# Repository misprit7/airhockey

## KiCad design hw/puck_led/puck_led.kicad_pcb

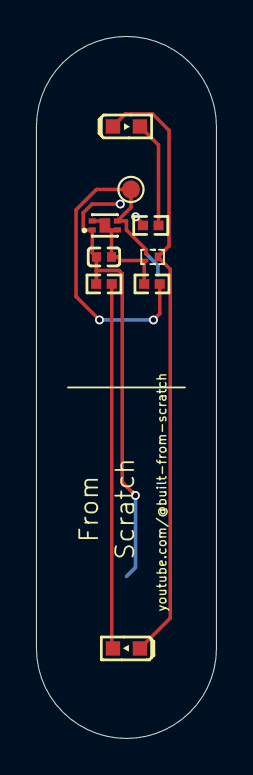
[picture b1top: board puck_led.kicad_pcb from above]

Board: 2 copper layers, 10.0 x 39.0 mm, 9 parts (0 on the bottom side), 6 nets.

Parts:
C1: 100nF; C0402
LED1, LED2: OPTO-SMD_L1.6-W0.8_E6C0603IRAC1UDA_1
Q1: PICOSTAR-3_L1.0-W0.6-P0.35-TL
R1: 100kΩ; R0402
R2, R3: 150Ω; R0402
TP1: TestPoint; TestPoint_Pad_D1.0mm
U1: XFDFN-4_L1.4-W1.1-P0.50-BL-EP

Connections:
+3V0: C1.2, R2.2, R3.2, U1.1 (VCC)
GND: C1.1, Q1.2 (S), R1.1, U1.2 (GND), U1.4 (SEL), U1.5 (EP)
unnamed: LED1.2 (A), R2.1
unnamed: LED1.1 (C), LED2.1 (C), Q1.3 (D)
unnamed: LED2.2 (A), R3.1
unnamed: Q1.1 (G), R1.2, TP1.1 (1_1), U1.3 (OUT)

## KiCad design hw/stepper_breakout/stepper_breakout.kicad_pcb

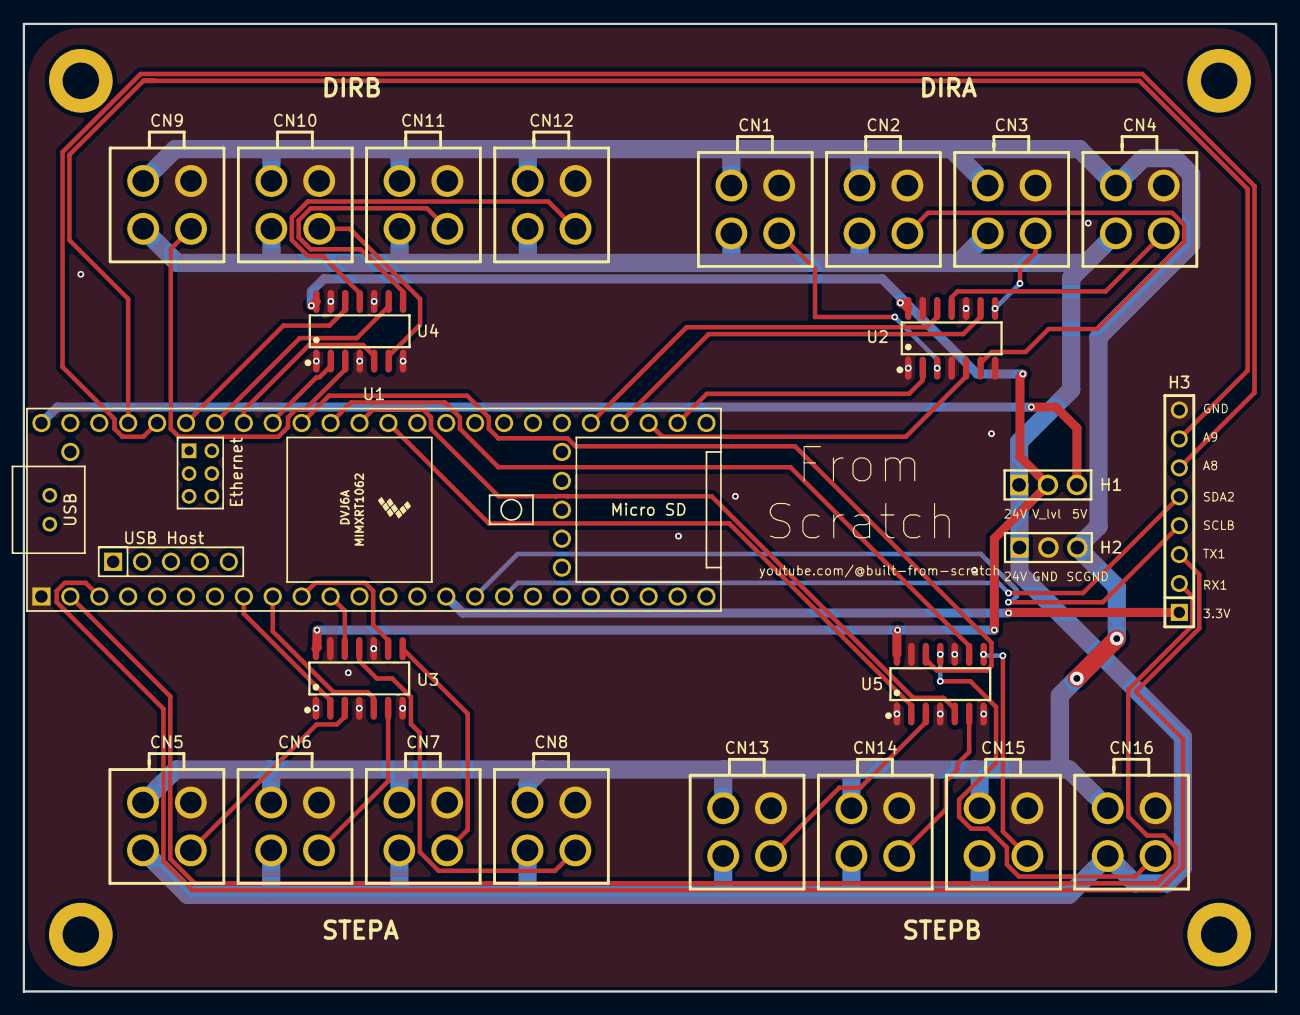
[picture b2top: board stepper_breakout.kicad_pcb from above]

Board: 2 copper layers, 110.0 x 85.0 mm, 24 parts (0 on the bottom side), 44 nets.

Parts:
CN1, CN2, CN3, CN4, CN5, CN6, CN7, CN8, CN9, CN10, CN11, CN12, CN13, CN14, CN15, CN16: CONN-TH_HAA420A-4A
H1, H2: HDR-TH_3P-P2.54-V-M-1
H3: HDR-TH_8P-P2.54-V-M
U1: Teensy4.1; Teensy41
U2, U3, U4, U5: SOIC-14_L8.7-W3.9-P1.27-LS6.0-BL

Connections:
+3V3: H3.1, U1.15 (3V3)
+5V: H1.3, U1.48 (VIN)
/A8: H3.6, U1.44 (22_A8_CTX1)
/A9: H3.7, U1.45 (23_A9_CRX1_MCLK1)
/DIR0: U1.26 (34_RX8), U2.2 (1A)
/DIR0B: U1.40 (18_A4_SDA), U4.2 (1A)
/DIR1: U1.27 (35_TX8), U2.5 (2A)
/DIR1B: U1.41 (19_A5_SCL), U4.5 (2A)
/DIR2: U1.28 (36_CS), U2.9 (3A)
/DIR2B: U1.42 (20_A6_TX5_LRCLK1), U4.9 (3A)
/DIR3: U1.29 (37_CS), U2.12 (4A)
/DIR3B: U1.43 (21_A7_RX5_BCLK1), U4.12 (4A)
/RX1: H3.2, U1.2 (0_RX1_CRX2_CS1)
/SCL2: H3.4, U1.16 (24_A10_TX6_SCL2)
/SDA2: H3.5, U1.17 (25_A11_RX6_SDA2)
/STEP0: U1.8 (6_OUT1D), U3.2 (1A)
/STEP0B: U1.36 (14_A0_TX3_SPDIF_OUT), U5.2 (1A)
/STEP1: U1.9 (7_RX2_OUT1A), U3.5 (2A)
/STEP1B: U1.37 (15_A1_RX3_SPDIF_IN), U5.5 (2A)
/STEP2: U1.10 (8_TX2_IN1), U3.9 (3A)
/STEP2B: U1.38 (16_A2_RX4_SCL1), U5.9 (3A)
/STEP3: U1.11 (9_OUT1C), U3.12 (4A)
/STEP3B: U1.39 (17_A3_TX4_SDA1), U5.12 (4A)
/TX1: H3.3, U1.3 (1_TX1_CTX2_MISO1)
/output1/OUT0: CN5.3, U3.3 (1Y)
/output1/OUT1: CN6.3, U3.6 (2Y)
/output1/OUT2: CN7.3, U3.8 (3Y)
/output1/OUT3: CN8.3, U3.11 (4Y)
/output2/OUT0: CN9.3, U4.3 (1Y)
/output2/OUT1: CN10.3, U4.6 (2Y)
/output2/OUT2: CN11.3, U4.8 (3Y)
/output2/OUT3: CN12.3, U4.11 (4Y)
/output3/OUT0: CN13.3, U5.3 (1Y)
/output3/OUT1: CN14.3, U5.6 (2Y)
/output3/OUT2: CN15.3, U5.8 (3Y)
/output3/OUT3: CN16.3, U5.11 (4Y)
/output/OUT0: CN1.3, U2.3 (1Y)
/output/OUT1: CN2.3, U2.6 (2Y)
/output/OUT2: CN3.3, U2.8 (3Y)
/output/OUT3: CN4.3, U2.11 (4Y)
GND: CN1.4, CN2.4, CN3.4, CN4.4, CN5.4, CN6.4, CN7.4, CN8.4, CN9.4, CN10.4, CN11.4, CN12.4, CN13.4, CN14.4, CN15.4, CN16.4, H2.2, H3.8, U1.1 (GND), U2.1 (1OE#), U2.4 (2OE#), U2.7 (GND), U2.10 (3OE#), U2.13 (4OE#), U3.1 (1OE#), U3.4 (2OE#), U3.7 (GND), U3.10 (3OE#), U3.13 (4OE#), U4.1 (1OE#), U4.4 (2OE#), U4.7 (GND), U4.10 (3OE#), U4.13 (4OE#), U5.1 (1OE#), U5.4 (2OE#), U5.7 (GND), U5.10 (3OE#), U5.13 (4OE#)
SC24V: CN1.1, CN2.1, CN3.1, CN4.1, CN5.1, CN6.1, CN7.1, CN8.1, CN9.1, CN10.1, CN11.1, CN12.1, CN13.1, CN14.1, CN15.1, CN16.1, H1.1, H2.1
SCGND: CN1.2, CN2.2, CN3.2, CN4.2, CN5.2, CN6.2, CN7.2, CN8.2, CN9.2, CN10.2, CN11.2, CN12.2, CN13.2, CN14.2, CN15.2, CN16.2, H2.3
V_lvl: H1.2, U2.14 (VCC), U3.14 (VCC), U4.14 (VCC), U5.14 (VCC)
